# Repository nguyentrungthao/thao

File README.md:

# Cách viết README 

## Tạo bảng 
|STT        |Tên            |
|-----------|---------------|
|1          |Nguyễn Trung Thảo|

## Add hình vào readme 

## Tạo chỗ copy trong README
```
Nguyễn Trung Thảo 20151564

nội dung copy nhanh trên README 

```

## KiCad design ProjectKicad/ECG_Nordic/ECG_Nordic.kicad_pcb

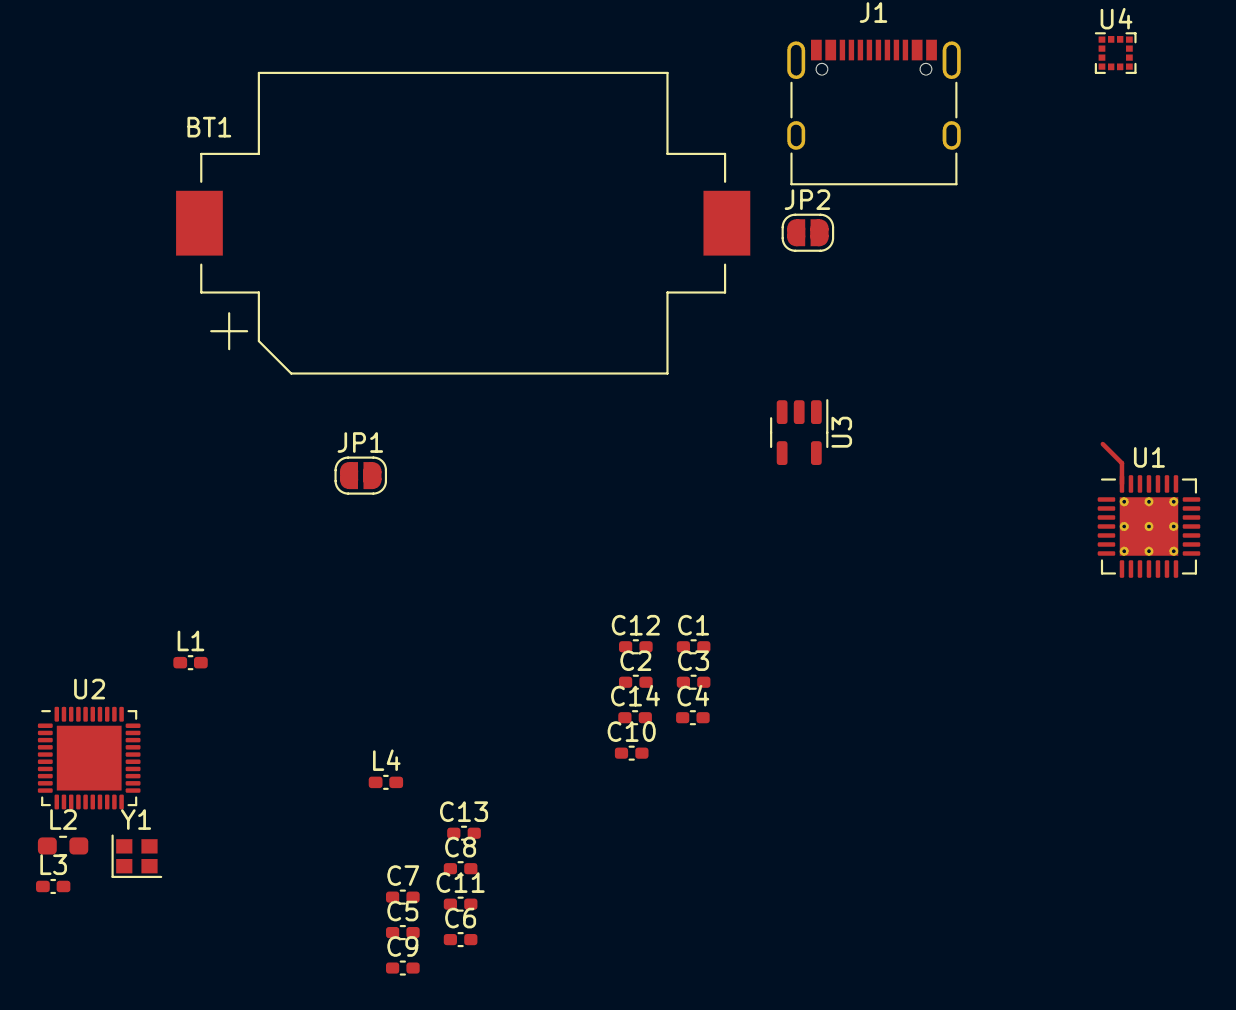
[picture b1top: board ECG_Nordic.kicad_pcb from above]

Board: 2 copper layers, 27 parts (0 on the bottom side), 7 nets.

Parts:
BT1: 3.3V_CR2032; BatteryHolder_Keystone_1060_1x2032
C1, C2: 4.7uF; C_0402_1005Metric_Pad0.74x0.62mm_HandSolder
C3, C4, C6, C7: 12pF; C_0402_1005Metric_Pad0.74x0.62mm_HandSolder
C5: 820pF; C_0402_1005Metric_Pad0.74x0.62mm_HandSolder
C8: 100pF; C_0402_1005Metric_Pad0.74x0.62mm_HandSolder
C9: 1uF; C_0402_1005Metric_Pad0.74x0.62mm_HandSolder
C10: 1pF; C_0402_1005Metric_Pad0.74x0.62mm_HandSolder
C11: 1.2pF; C_0402_1005Metric_Pad0.74x0.62mm_HandSolder
C12, C13, C14: 100nF; C_0402_1005Metric_Pad0.74x0.62mm_HandSolder
J1: USB_C_Receptacle; USB_C_Receptacle_XKB_U262-16XN-4BVC11
JP1, JP2: SolderJumper_2_Open; SolderJumper-2_P1.3mm_Open_RoundedPad1.0x1.5mm
L1: 15nH; L_0402_1005Metric_Pad0.77x0.64mm_HandSolder
L2: 10uH; L_0603_1608Metric_Pad1.05x0.95mm_HandSolder
L3: 4.7nH; L_0402_1005Metric_Pad0.77x0.64mm_HandSolder
L4: 2.2nH; L_0402_1005Metric_Pad0.77x0.64mm_HandSolder
U1: MAX30003CTI+; TQFN-28-1EP_5x5mm_P0.5mm_EP3.25x3.25mm_ThermalVias
U2: nRF52820-QDxx; QFN-40-1EP_5x5mm_P0.4mm_EP3.6x3.6mm
U3: RT9193-18GB; SOT-23-5
U4: MC3419; LGA-12_2x2mm_P0.5mm
Y1: Crystal_GND23; Crystal_SMD_2016-4Pin_2.0x1.6mm

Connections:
+1V8: JP2.1 (A), U3.5 (VOUT), U4.7 (VDD)
+5V: JP2.2 (B), U3.1 (VIN)
/Power/D+: J1.A6 (D+), J1.B6 (D+)
/Power/D-: J1.A7 (D-), J1.B7 (D-)
GND: BT1.2 (-), J1.A1 (GND), J1.A12 (GND), J1.B1 (GND), J1.B12 (GND), J1.S1 (SHIELD), U1.3 (AGND), U1.8 (AGND), U1.12 (DGND), U1.28 (AGND), U1.29 (EPAD), U3.2 (GND), U4.9 (GND)
unnamed: U2.37 (VSS), U2.41 (VSS)
VBUS: J1.A4 (VBUS), J1.A9 (VBUS), J1.B4 (VBUS), J1.B9 (VBUS)

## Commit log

2022-10-21 update-ECG
2022-12-02 change git to leanr write README.md
2022-12-02 change name readme.md
2022-12-02 add link diver of picture
2022-12-06 kkkkkkkkkkkkkkkkkkkkkkkkkkkkkkkkkkkkkkkkkkkkkkkkkkkkkkkkkkkkkkkkkkkkkkkkkkkkkkkkkkkkkkkkkkkkkkkkkkkkkkkkkkkkkkkkkkkkkkkkkkkkkkkkkkkkkkkkkkkkkkkkkkkkkkkkkkkkkkkkkkkkkkkkkkkkkkkkkkkkkkkkkkkkkkkkkkkkkkk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
2022-12-06 heehello
    hjhfasjhdfljashdfsadfasdfasdjkhskd
    ádfa
    sdfsad
    fas
    df
    á
